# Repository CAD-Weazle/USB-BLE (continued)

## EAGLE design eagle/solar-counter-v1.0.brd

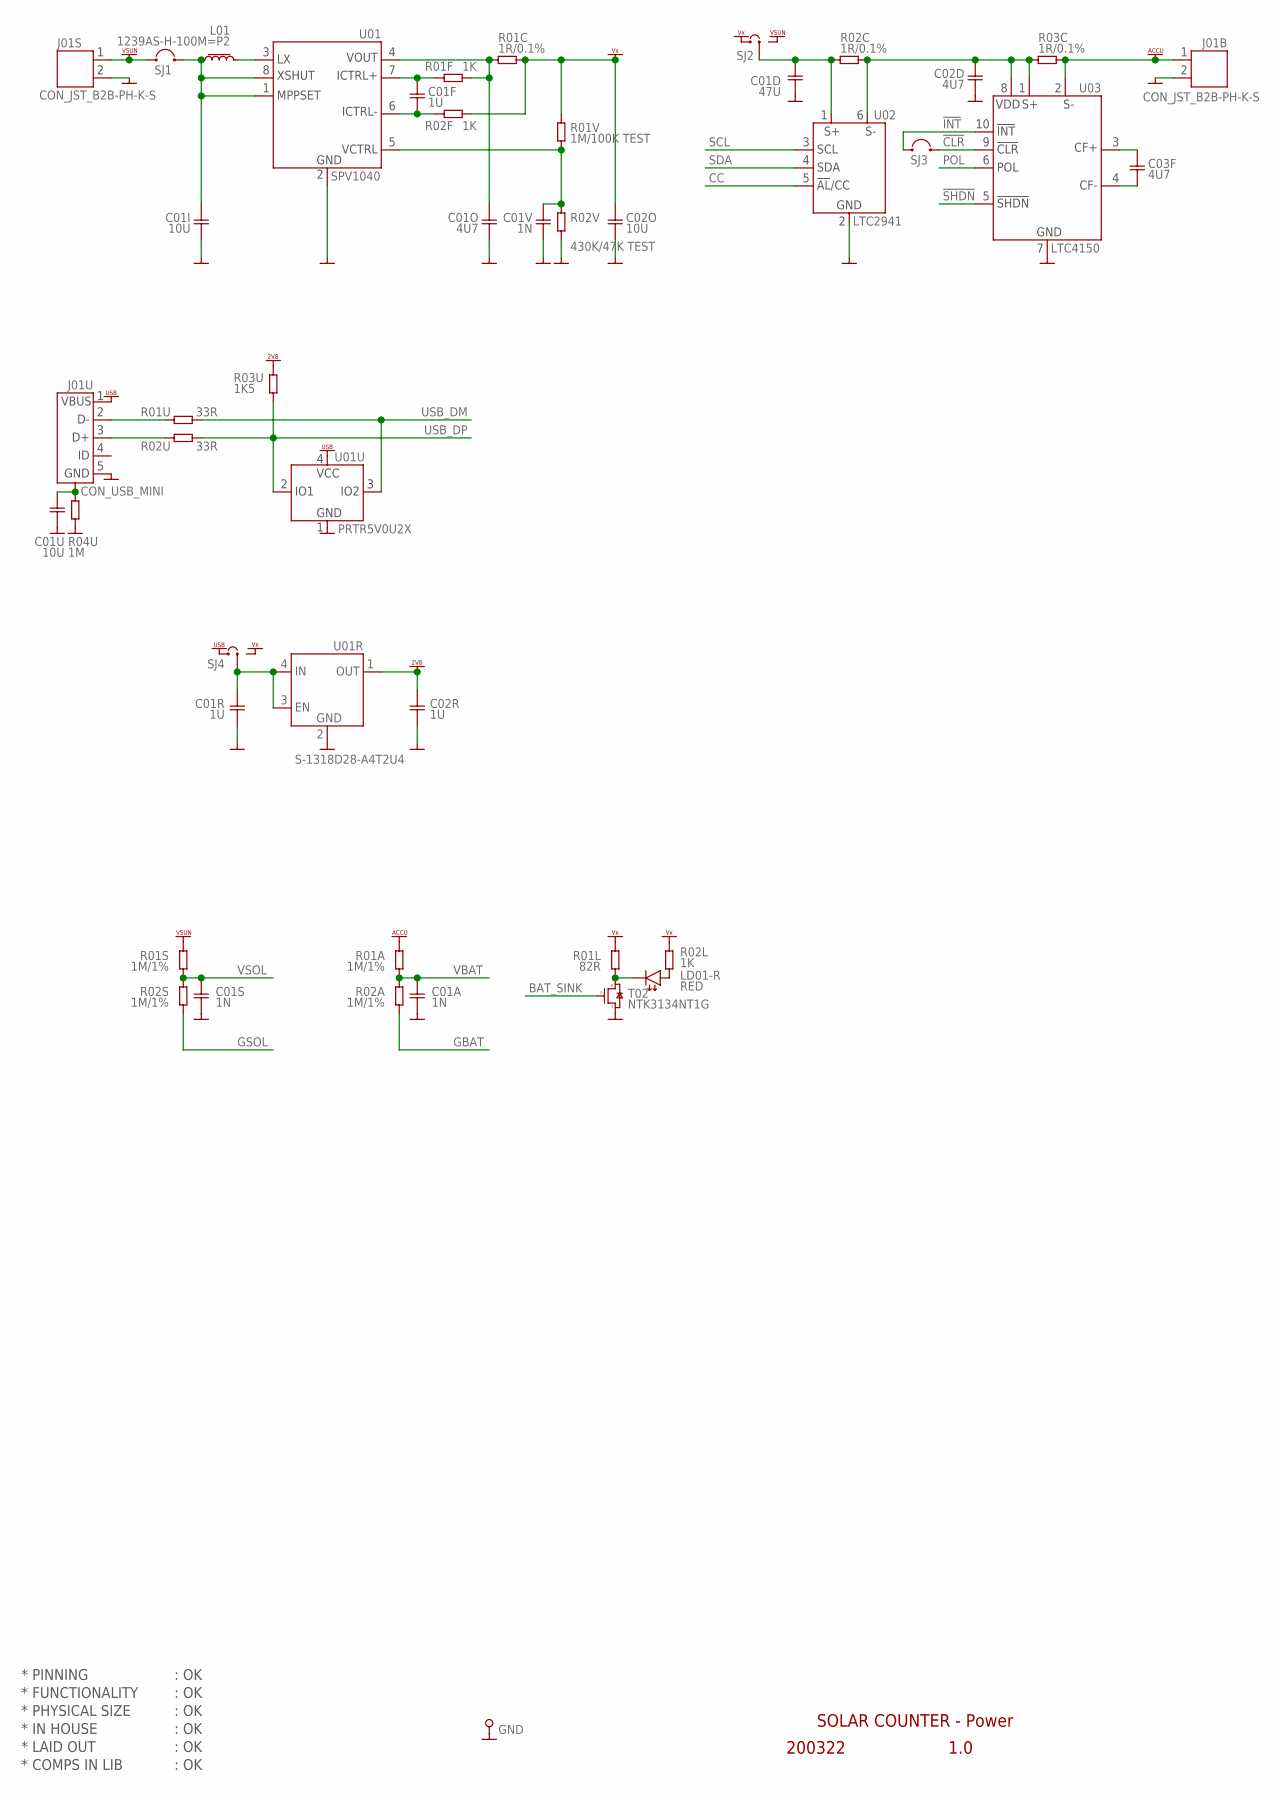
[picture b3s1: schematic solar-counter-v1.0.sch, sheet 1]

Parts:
C01A, C01S, C01V: 1N; CAP0402
C01D: 47U; CAP0603
C01F, C01R, C02R: 1U; CAP0402
C01I, C01U: 10U; CAP0603
C01O, C02D, C03F: 4U7; CAP0402
C02O: 10U; CAP0402
GND: PIN_TEST; HOLE_PTH_0.8MM
J01B, J01S: CON_JST_B2B-PH-K-S
J01U: CON_USB_MINI; CON_USB-B_MINI
L01: 1239AS-H-100M=P2; L_1008
LD01-R: RED; LED_SMD_0402
R01A, R01S, R02A, R02S: 1M/1%; RES0402
R01C, R02C, R03C: 1R/0.1%; RES0402
R01F, R02F, R02L: 1K; RES0402
R01L: 82R; RES0402
R01U, R02U: 33R; RES0402
R01V: 1M/100K TEST; RES0402
R02V: 430K/47K TEST; RES0402
R03U: 1K5; RES0402
R04U: 1M; RES0603
SJ1, SJ3: SJ2SJ2-S; SJ2-S
SJ2, SJ4: SJ3SJ3-S; SJ3-S
T02: NTK3134NT1G; NFET_SOT723
U01: SPV1040; TSSOP8
U01R: S-1318D28-A4T2U4; HSNT-4-B
U01U: PRTR5V0U2X; SOT143B
U02: LTC2941; DFN6_2X3MM_NO-EXPOSED
U03: LTC4150; MSOP10

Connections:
!CLR: SJ3.2, U03.9 (9.!CLR); also elsewhere on the board
!INT: SJ3.1, U03.10 (10.!INT); also elsewhere on the board
!SHDN: U03.5 (5.!SHDN); also elsewhere on the board
ACCU: J01B.1, R01A.2, R03C.2, U03.2 (2.SENSE-)
BAT_SINK: T02.1 (1.G); also elsewhere on the board
CC: U02.5 (5.AL/CC); also elsewhere on the board
GBAT: R02A.1; also elsewhere on the board
GND: C01A.2, C01D.2, C01I.2, C01O.2, C01R.2, C01S.2, C01U.2, C01V.2, C02D.2, C02O.2, C02R.2, GND.1, J01B.2, J01S.2, J01U.5 (5.GND), R02V.2, R04U.2, T02.2 (2.S), U01.2 (2.GND), U01R.2 (2.GND), U01R.5 (2.GND), U01U.1 (1.GND), U02.2 (2.GND), U03.7 (7.GND); also elsewhere on the board
GSOL: R02S.1; also elsewhere on the board
unnamed: C01D.1, R02C.1, SJ2.2, U02.1 (1.SENSE+)
unnamed: LD01-R.A, R02L.2
unnamed: C01F.2, R02F.2, U01.6 (6.ICTRL-)
unnamed: C02D.1, R02C.2, R03C.1, U02.6 (6.SENSE-), U03.1 (1.SENSE+), U03.8 (8.VDD)
unnamed: C01I.1, L01.2, SJ1.2, U01.1 (1.MPPSET), U01.8 (8.XSHUT)
unnamed: LD01-R.C, R01L.1, T02.3 (3.D)
unnamed: C01F.1, R01F.2, U01.7 (7.ICTRL+)
unnamed: L01.1, U01.3 (3.LX)
unnamed: C03F.2, U03.4 (4.CF-)
unnamed: C03F.1, U03.3 (3.CF+)
unnamed: J01U.2 (2.D-), R01U.1
unnamed: J01U.3 (3.D+), R02U.1
POL: U03.6 (6.POL); also elsewhere on the board
SCL: U02.3 (3.SCL); also elsewhere on the board
SDA: U02.4 (4.SDA); also elsewhere on the board
USB_CHASSIS: C01U.1, J01U.CASE1 (CASE), J01U.CASE2 (CASE), J01U.CASE3 (CASE), J01U.CASE4 (CASE), R04U.1
USB_DM: R01U.2, U01U.3 (3.IO2); also elsewhere on the board
USB_DP: R02U.2, R03U.1, U01U.2 (2.IO1); also elsewhere on the board
VBAT: C01A.1, R01A.1, R02A.2; also elsewhere on the board
VDD_2V8: C02R.1, R03U.2, U01R.1 (1.OUT); also elsewhere on the board
VDD_USB: J01U.1 (1.VBUS), SJ4.1, U01U.4 (4.VCC)
VIN: C01R.1, SJ4.2, U01R.3 (3.EN), U01R.4 (4.IN)
VOUT: C01O.1, R01C.1, R01F.1, U01.4 (4.VOUT)
VOUT_SET: C01V.1, R01V.2, R02V.1, U01.5 (5.VCTRL)
VSOL: C01S.1, R01S.1, R02S.2; also elsewhere on the board
VSUN: J01S.1, R01S.2, SJ1.1, SJ2.3
VX: C02O.1, R01C.2, R01L.2, R01V.1, R02F.1, R02L.1, SJ2.1, SJ4.3

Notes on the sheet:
* PINNING
* FUNCTIONALITY
* PHYSICAL SIZE
* LAID OUT
* COMPS IN LIB
* IN HOUSE
SOLAR COUNTER - Power
200322
1.0
: OK

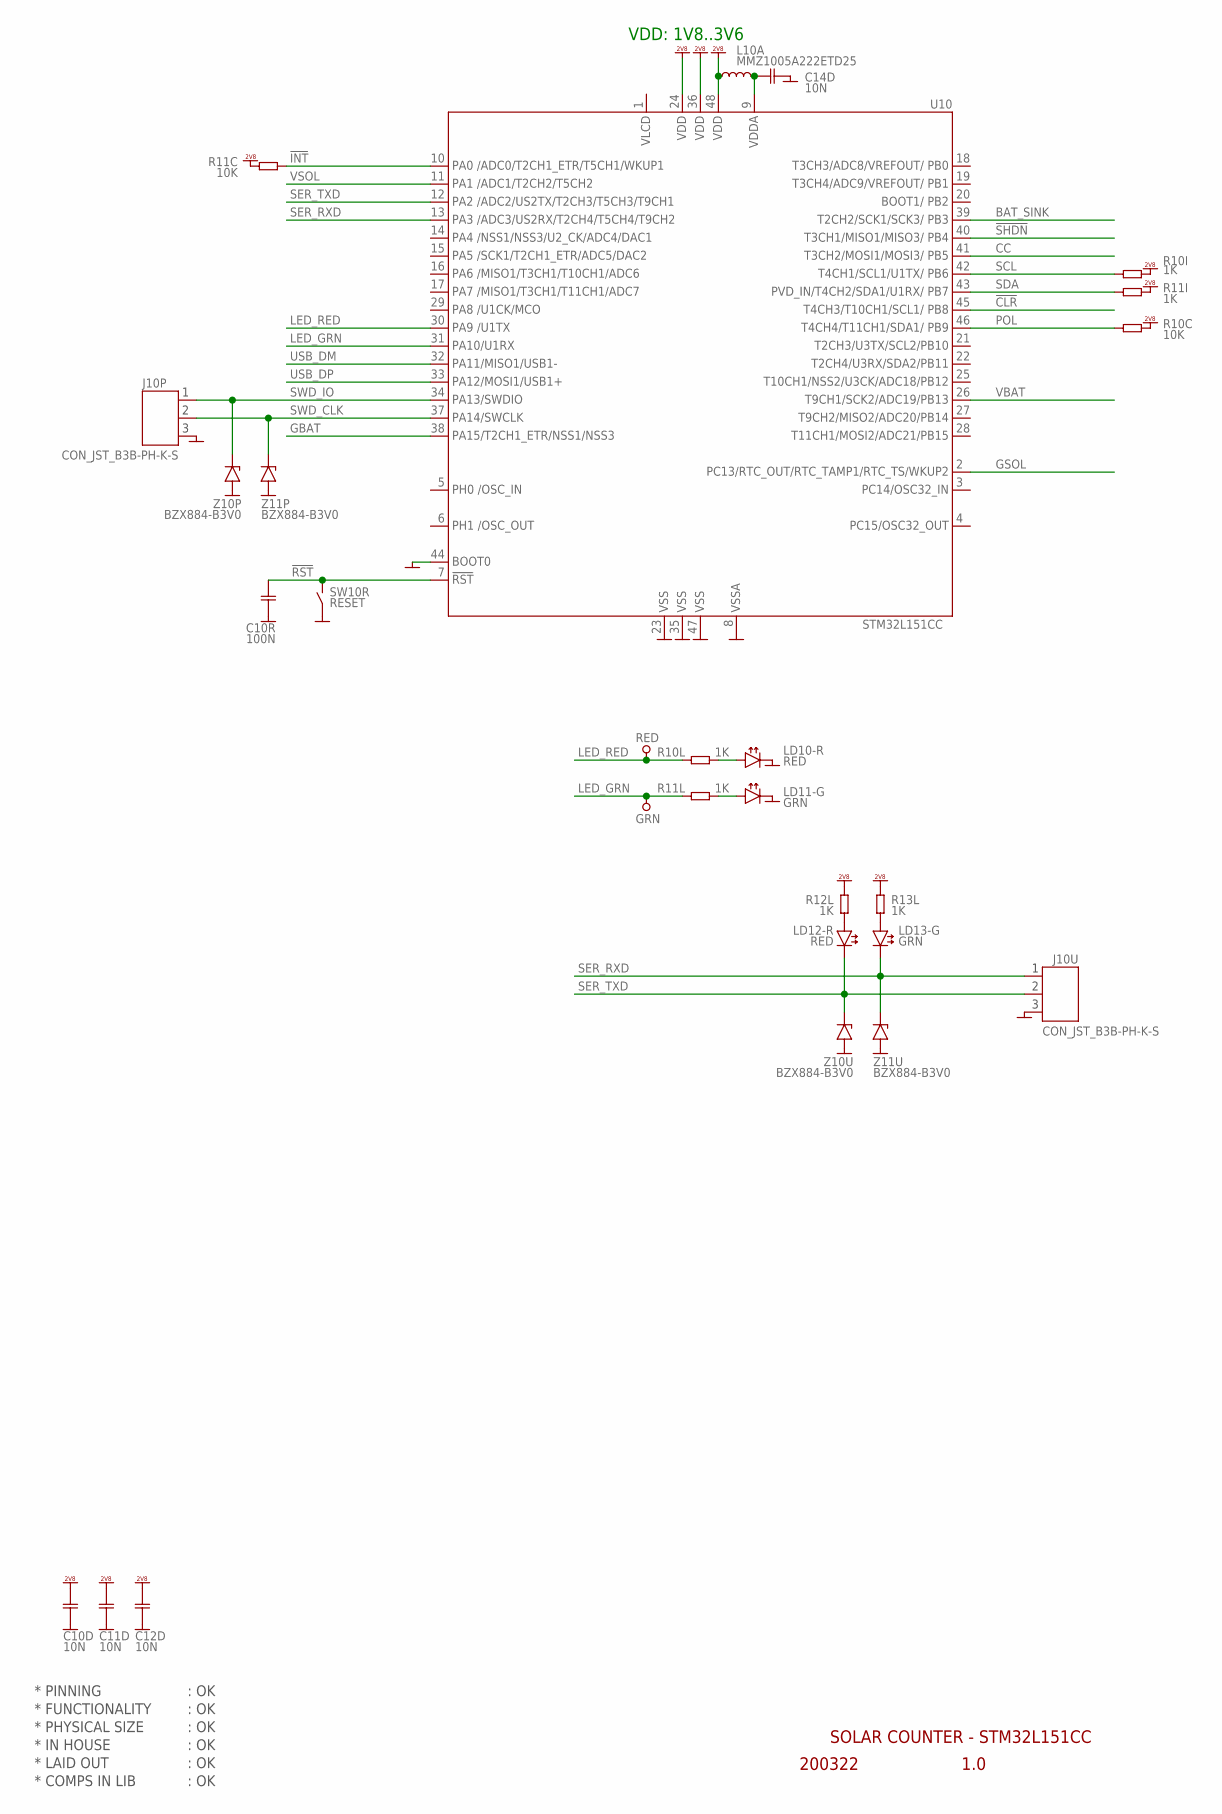
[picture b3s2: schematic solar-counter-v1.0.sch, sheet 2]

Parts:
C10D, C11D, C12D, C14D: 10N; CAP0402
C10R: 100N; CAP0402
GRN: PIN_TEST_0.6MM; HOLE_PTH_0.6MM
J10P, J10U: CON_JST_B3B-PH-K-S
L10A: MMZ1005A222ETD25; L_0402
LD10-R, LD12-R: RED; LED_SMD_0402
LD11-G, LD13-G: GRN; LED_SMD_0402
R10C, R11C: 10K; RES0402
R10I, R10L, R11I, R11L, R12L, R13L: 1K; RES0402
RED: PIN_TEST_0.6MM; HOLE_PTH_0.6MM
SW10R: RESET; SWITCH_SMD_PBUTTON_2P
U10: STM32L151CC; LQFP48
Z10P, Z10U, Z11P, Z11U: BZX884-B3V0; ZENER_SOD923

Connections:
!CLR: U10.45 (45.PB8); also elsewhere on the board
!INT: R11C.1, U10.10 (10.PA0); also elsewhere on the board
!RST: C10R.1, SW10R.1 (1-2), U10.7 (7.!RST)
!SHDN: U10.40 (40.PB4); also elsewhere on the board
BAT_SINK: U10.39 (39.PB3); also elsewhere on the board
CC: U10.41 (41.PB5); also elsewhere on the board
GBAT: U10.38 (38.PA15); also elsewhere on the board
GND: C10D.2, C10R.2, C11D.2, C12D.2, C14D.2, J10P.3, J10U.3, LD10-R.C, LD11-G.C, SW10R.2 (3-4), U10.8 (8.GND), U10.23 (23.GND), U10.35 (35.GND), U10.44 (44.BOOT0), U10.47 (47.GND), Z10P.2 (A), Z10U.2 (A), Z11P.2 (A), Z11U.2 (A); also elsewhere on the board
GSOL: U10.2 (2.PC13); also elsewhere on the board
LED_GRN: GRN.1, R11L.1, U10.31 (31.PA10)
LED_RED: R10L.1, RED.1, U10.30 (30.PA9)
unnamed: LD13-G.A, R13L.2
unnamed: LD12-R.A, R12L.2
unnamed: LD11-G.A, R11L.2
unnamed: LD10-R.A, R10L.2
POL: R10C.1, U10.46 (46.PB9); also elsewhere on the board
SCL: R10I.1, U10.42 (42.PB6); also elsewhere on the board
SDA: R11I.1, U10.43 (43.PB7); also elsewhere on the board
SER_RXD: J10U.1, LD13-G.C, U10.13 (13.PA3), Z11U.1 (C)
SER_TXD: J10U.2, LD12-R.C, U10.12 (12.PA2), Z10U.1 (C)
SWD_CLK: J10P.2, U10.37 (37.PA14), Z11P.1 (C)
SWD_IO: J10P.1, U10.34 (34.PA13), Z10P.1 (C)
USB_DM: U10.32 (32.PA11); also elsewhere on the board
USB_DP: U10.33 (33.PA12); also elsewhere on the board
VBAT: U10.26 (26.PB13); also elsewhere on the board
VDDA: C14D.1, L10A.2, U10.9 (9.VDD)
VDD_2V8: C10D.1, C11D.1, C12D.1, L10A.1, R10C.2, R10I.2, R11C.2, R11I.2, R12L.1, R13L.1, U10.24 (24.VDD), U10.36 (36.VDD), U10.48 (48.VDD); also elsewhere on the board
VSOL: U10.11 (11.PA1); also elsewhere on the board

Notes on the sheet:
* PINNING
* FUNCTIONALITY
* PHYSICAL SIZE
* LAID OUT
* COMPS IN LIB
* IN HOUSE
: OK
SOLAR COUNTER - STM32L151CC
200322
1.0
VDD: 1V8..3V6

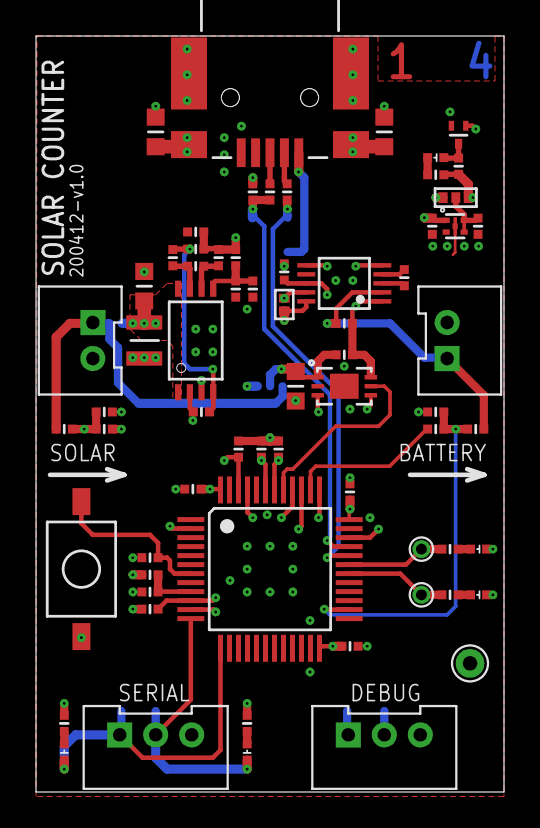
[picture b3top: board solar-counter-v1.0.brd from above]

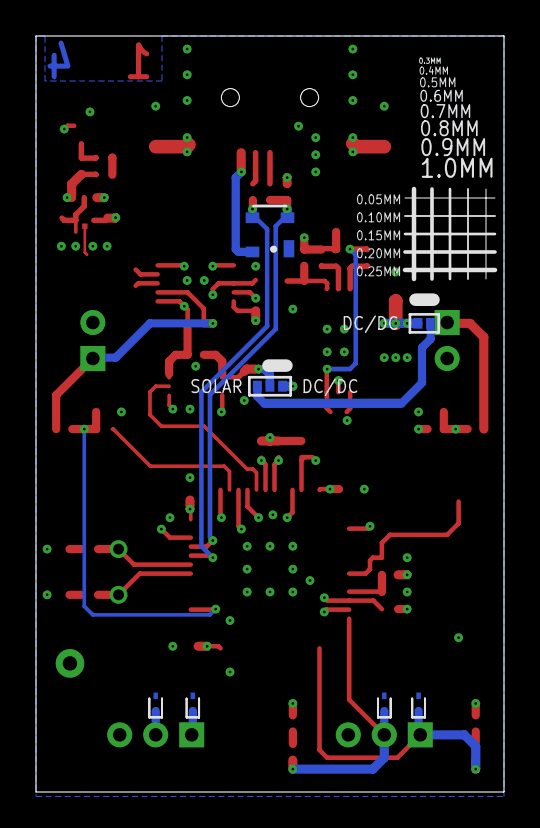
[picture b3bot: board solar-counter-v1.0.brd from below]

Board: 4 copper layers, 26.0 x 42.0 mm, 74 parts (7 on the bottom side), 48 nets.

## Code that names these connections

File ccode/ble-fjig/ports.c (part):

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static const struct port_info porta[16] = 
{
  [ 0] = {GPIO_MODE_IN,  GPIO_SPEED_FREQ_LOW,  GPIO_OTYPE_PP, GPIO_PULLUP},                  // BLE_TXI_L
  [ 1] = {GPIO_MODE_AN,  GPIO_SPEED_FREQ_LOW,  GPIO_OTYPE_PP, GPIO_NOPULL},                  // BLE_CUR    - ADC[1]
  [ 2] = {GPIO_MODE_AF,  GPIO_SPEED_FREQ_LOW,  GPIO_OTYPE_PP, GPIO_PULLUP, GPIO_AF7_USART2}, // SER_TXD
  [ 3] = {GPIO_MODE_AF , GPIO_SPEED_FREQ_LOW,  GPIO_OTYPE_PP, GPIO_PULLUP, GPIO_AF7_USART2}, // SER_RXD
  [ 4] = {GPIO_MODE_AN,  GPIO_SPEED_FREQ_LOW,  GPIO_OTYPE_PP, GPIO_NOPULL},                  // LIGHT_OUT  - ADC[4]
  [ 5] = {GPIO_MODE_IN,  GPIO_SPEED_FREQ_LOW,  GPIO_OTYPE_PP, GPIO_PULLDOWN},                // NU
  [ 6] = {GPIO_MODE_IN,  GPIO_SPEED_FREQ_LOW,  GPIO_OTYPE_PP, GPIO_PULLDOWN},                // NU
  [ 7] = {GPIO_MODE_IN,  GPIO_SPEED_FREQ_LOW,  GPIO_OTYPE_PP, GPIO_PULLDOWN},                // NU
  [ 8] = {GPIO_MODE_AF,  GPIO_SPEED_FREQ_LOW,  GPIO_OTYPE_PP, GPIO_NOPULL, GPIO_AF0_MCO},    // CLOCK_OUT  - MCO
  [ 9] = {GPIO_MODE_OUT, GPIO_SPEED_FREQ_LOW,  GPIO_OTYPE_PP, GPIO_NOPULL},                  // LED_RED
  [10] = {GPIO_MODE_OUT, GPIO_SPEED_FREQ_LOW,  GPIO_OTYPE_PP, GPIO_NOPULL},                  // LED_GRN
  [11] = {GPIO_MODE_OUT, GPIO_SPEED_FREQ_LOW,  GPIO_OTYPE_OD, GPIO_NOPULL},                  // VGND (open drain)
  [12] = {GPIO_MODE_IN,  GPIO_SPEED_FREQ_LOW,  GPIO_OTYPE_PP, GPIO_PULLDOWN},                // NU
  [13] = {GPIO_MODE_AF,  GPIO_SPEED_FREQ_HIGH, GPIO_OTYPE_PP, GPIO_NOPULL, GPIO_AF0_SWJ},    // SWD_IO
  [14] = {GPIO_MODE_AF,  GPIO_SPEED_FREQ_HIGH, GPIO_OTYPE_PP, GPIO_NOPULL, GPIO_AF0_SWJ},    // SWD_CLK 
  [15] = {GPIO_MODE_OUT, GPIO_SPEED_FREQ_LOW,  GPIO_OTYPE_PP, GPIO_NOPULL},                  // BAT_SINK
};

// GPIO Port A settings - STOP mode
static const struct port_info stopa[16] = 
{
  [ 0] = {GPIO_MODE_IN,  GPIO_SPEED_FREQ_LOW, GPIO_OTYPE_PP, GPIO_PULLUP},                   // BLE_TXI_L  - keep input for EXTI event 
  [ 1] = {GPIO_MODE_AN,  GPIO_SPEED_FREQ_LOW, GPIO_OTYPE_PP, GPIO_PULLDOWN},                 // BLE_CUR    - ADC[1]
  [ 2] = {GPIO_MODE_AF,  GPIO_SPEED_FREQ_LOW, GPIO_OTYPE_PP, GPIO_PULLUP,  GPIO_AF7_USART2}, // SER_TXD    - don't change function, keep TxD high
  [ 3] = {GPIO_MODE_AN,  GPIO_SPEED_FREQ_LOW, GPIO_OTYPE_PP, GPIO_PULLUP},                   // SER_RXD
  [ 4] = {GPIO_MODE_AN,  GPIO_SPEED_FREQ_LOW, GPIO_OTYPE_PP, GPIO_PULLDOWN},                 // 
  [ 5] = {GPIO_MODE_AN,  GPIO_SPEED_FREQ_LOW, GPIO_OTYPE_PP, GPIO_PULLDOWN},                 // 
  [ 6] = {GPIO_MODE_AN,  GPIO_SPEED_FREQ_LOW, GPIO_OTYPE_PP, GPIO_PULLDOWN},                 // 
  [ 7] = {GPIO_MODE_AN,  GPIO_SPEED_FREQ_LOW, GPIO_OTYPE_PP, GPIO_PULLDOWN},                 // 
  [ 8] = {GPIO_MODE_AN,  GPIO_SPEED_FREQ_LOW, GPIO_OTYPE_PP, GPIO_PULLDOWN},                 // 
  [ 9] = {GPIO_MODE_AN,  GPIO_SPEED_FREQ_LOW, GPIO_OTYPE_PP, GPIO_PULLDOWN},                 // 
  [10] = {GPIO_MODE_AN,  GPIO_SPEED_FREQ_LOW, GPIO_OTYPE_PP, GPIO_NOPULL},                   // VGND         - open drain
  [11] = {GPIO_MODE_AN,  GPIO_SPEED_FREQ_LOW, GPIO_OTYPE_PP, GPIO_PULLDOWN},                 // 
  [12] = {GPIO_MODE_AN,  GPIO_SPEED_FREQ_LOW, GPIO_OTYPE_PP, GPIO_PULLDOWN},                 // 
  [13] = {GPIO_MODE_IN,  GPIO_SPEED_FREQ_LOW, GPIO_OTYPE_PP, GPIO_PULLDOWN},                 // SWD_IO
  [14] = {GPIO_MODE_IN,  GPIO_SPEED_FREQ_LOW, GPIO_OTYPE_PP, GPIO_PULLDOWN},                 // SWD_CLK
  [15] = {GPIO_MODE_AN,  GPIO_SPEED_FREQ_LOW, GPIO_OTYPE_PP, GPIO_PULLDOWN},                 // 
};

// GPIO Port B settings
static const struct port_info portb[16] = 
{
  [ 0] = {GPIO_MODE_IN,  GPIO_SPEED_FREQ_LOW,  GPIO_OTYPE_PP, GPIO_PULLUP},                  // BLE_MODE
  [ 1] = {GPIO_MODE_OUT, GPIO_SPEED_FREQ_LOW,  GPIO_OTYPE_PP, GPIO_PULLUP},                  // BLE_RESET_L
  [ 2] = {GPIO_MODE_IN,  GPIO_SPEED_FREQ_LOW,  GPIO_OTYPE_PP, GPIO_PULLDOWN},                // NU
  [ 3] = {GPIO_MODE_IN,  GPIO_SPEED_FREQ_LOW,  GPIO_OTYPE_PP, GPIO_PULLDOWN},                // NU
  [ 4] = {GPIO_MODE_IN,  GPIO_SPEED_FREQ_LOW,  GPIO_OTYPE_PP, GPIO_PULLDOWN},                // NU
  [ 5] = {GPIO_MODE_IN,  GPIO_SPEED_FREQ_LOW,  GPIO_OTYPE_PP, GPIO_PULLDOWN},                // NU
  [ 6] = {GPIO_MODE_IN,  GPIO_SPEED_FREQ_LOW,  GPIO_OTYPE_PP, GPIO_PULLDOWN},                // NU
  [ 7] = {GPIO_MODE_OUT, GPIO_SPEED_FREQ_LOW,  GPIO_OTYPE_OD, GPIO_NOPULL},                  // SHT_DAT
  [ 8] = {GPIO_MODE_OUT, GPIO_SPEED_FREQ_LOW,  GPIO_OTYPE_PP, GPIO_NOPULL},                  // SHT_CLK
  [ 9] = {GPIO_MODE_OUT, GPIO_SPEED_FREQ_LOW,  GPIO_OTYPE_PP, GPIO_NOPULL},                  // SENSOR_PWR_L
  [10] = {GPIO_MODE_AF,  GPIO_SPEED_FREQ_LOW,  GPIO_OTYPE_PP, GPIO_NOPULL, GPIO_AF7_USART3}, // BLE_RXD      - UART3
  [11] = {GPIO_MODE_AF,  GPIO_SPEED_FREQ_LOW,  GPIO_OTYPE_PP, GPIO_NOPULL, GPIO_AF7_USART3}, // BLE_TXD      - UART3
  [12] = {GPIO_MODE_OUT, GPIO_SPEED_FREQ_LOW,  GPIO_OTYPE_PP, GPIO_NOPULL},                  // BLE_RXI_L
  [13] = {GPIO_MODE_AN,  GPIO_SPEED_FREQ_LOW,  GPIO_OTYPE_PP, GPIO_NOPULL},                  // VBAT
  [14] = {GPIO_MODE_AN,  GPIO_SPEED_FREQ_LOW,  GPIO_OTYPE_PP, GPIO_NOPULL},                  // VSYS
  [15] = {GPIO_MODE_IN,  GPIO_SPEED_FREQ_LOW,  GPIO_OTYPE_PP, GPIO_PULLDOWN},                // NU
};

// GPIO Port B settings - STOP mode
static const struct port_info stopb[16] = 
{
   [0] = {GPIO_MODE_AN,  GPIO_SPEED_FREQ_LOW,  GPIO_OTYPE_PP, GPIO_PULLUP},                  // BLE_MODE     - keep high
   [1] = {GPIO_MODE_AN,  GPIO_SPEED_FREQ_LOW,  GPIO_OTYPE_PP, GPIO_PULLUP},                  // BLE_RESET_L  - keep high
   [2] = {GPIO_MODE_AN,  GPIO_SPEED_FREQ_LOW,  GPIO_OTYPE_PP, GPIO_PULLDOWN},                // 
   [3] = {GPIO_MODE_AN,  GPIO_SPEED_FREQ_LOW,  GPIO_OTYPE_PP, GPIO_PULLDOWN},                // 
   [4] = {GPIO_MODE_AN,  GPIO_SPEED_FREQ_LOW,  GPIO_OTYPE_PP, GPIO_PULLDOWN},                // 
   [5] = {GPIO_MODE_AN,  GPIO_SPEED_FREQ_LOW,  GPIO_OTYPE_PP, GPIO_PULLDOWN},                // 
   [6] = {GPIO_MODE_AN,  GPIO_SPEED_FREQ_LOW,  GPIO_OTYPE_PP, GPIO_PULLDOWN},                // 
   [7] = {GPIO_MODE_AN,  GPIO_SPEED_FREQ_LOW,  GPIO_OTYPE_PP, GPIO_PULLDOWN},                // SHT_DAT 
   [8] = {GPIO_MODE_AN,  GPIO_SPEED_FREQ_LOW,  GPIO_OTYPE_PP, GPIO_PULLDOWN},                // SHT_CLK
   [9] = {GPIO_MODE_AN,  GPIO_SPEED_FREQ_LOW,  GPIO_OTYPE_PP, GPIO_PULLDOWN},                // 
  [10] = {GPIO_MODE_AN,  GPIO_SPEED_FREQ_LOW,  GPIO_OTYPE_PP, GPIO_NOPULL},                  // BLE_RXD      - UART3
  [11] = {GPIO_MODE_AN,  GPIO_SPEED_FREQ_LOW,  GPIO_OTYPE_PP, GPIO_NOPULL},                  // BLE_TXD      - UART3
  [12] = {GPIO_MODE_AN,  GPIO_SPEED_FREQ_LOW,  GPIO_OTYPE_PP, GPIO_PULLDOWN},                // 
  [13] = {GPIO_MODE_AN,  GPIO_SPEED_FREQ_LOW,  GPIO_OTYPE_PP, GPIO_NOPULL},                  // VBAT
  [14] = {GPIO_MODE_AN,  GPIO_SPEED_FREQ_LOW,  GPIO_OTYPE_PP, GPIO_NOPULL},                  // VSYS
  [15] = {GPIO_MODE_AN,  GPIO_SPEED_FREQ_LOW,  GPIO_OTYPE_PP, GPIO_PULLDOWN},                // 
};

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// red LED routines
void led_red_on (void)
{
  gpio_set (GPIOA, LED_RED);
}

void led_red_off (void)
{
  gpio_clr (GPIOA, LED_RED);
}

void led_red_toggle (void)
{
  if (GPIOA->ODR & (1 << LED_RED))
    gpio_clr (GPIOA, LED_RED);
  else
    gpio_set (GPIOA, LED_RED);
}

void led_red_flash (uint16_t delay)
{
  gpio_set (GPIOA, LED_RED);
  msleep (delay);
  gpio_clr (GPIOA, LED_RED);
}

// green LED routines
void led_grn_on (void)
{
  gpio_set (GPIOA, LED_GRN);
}

void led_grn_off (void)
{
  gpio_clr (GPIOA, LED_GRN);
}

void led_grn_toggle (void)
{
  if (GPIOA->ODR & (1 << LED_GRN))
    gpio_clr (GPIOA, LED_GRN);
  else
    gpio_set (GPIOA, LED_GRN);
}

void led_grn_flash (uint16_t delay)
{
  gpio_set (GPIOA, LED_GRN);
  msleep (delay);
  gpio_clr (GPIOA, LED_GRN);
}

// connect dividers ground to GND
void vgnd_enable (void)
{
  gpio_clr (GPIOA, VGND);
}

// disconnect dividers ground from GND
void vgnd_disable (void)
{
  gpio_set (GPIOA, VGND);
}

// enable power to sensors
void sensor_power_enable (void)
{
  gpio_clr (GPIOB, SENSOR_PWR_L);
}

// disable power to sensors
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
